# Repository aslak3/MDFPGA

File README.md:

# MDFPGA: a HUB75 display controller base board using a Pi Pico W and an iCE40UP5K

A [schematic](MDFPGA.pdf) is included here, along with the [KiCAD](https://www.kicad.org)
data files, which are in KiCAD 6 format.

## PCB design

The PCB is a 4 layer board easily built by any random PCB house.

## Project overview

This board is the hardware for my Matrix Display project, which is spread across three repos: this one, [a repo holding the Pico W firmware](https://github.com/aslak3/matrix-display), and [an optional one that holds the HUB75 display controller](https://github.com/aslak3/hub75-controller), which is implemented in Verilog.

Once up and running, you will have a 64 x 32 LED matrix display, presenting information from your Home Assistant system or, in theory, any other system that publish data in a suitable format via MQTT.

## Hardware description

* Power via 5V barrel jack
* A Pi Pico W (obviously)
* A [DS3231](https://www.analog.com/media/en/technical-documentation/data-sheets/DS3231.pdf) (PDF) I2C Real Time Clock
  * CR122t battery backup
* IDC16 HUB75 connector attached to the Pico W
* Buzzer
* iCE40UP FPGA
  * [N25Q32A](https://www.mouser.co.uk/datasheet/2/12/Micron_Datasheet_N25Q032A_RevJ-1880047.pdf) (PDF) 32MBit SPI Flash
  * IDC16 HUB75 connector attached to the FPGA
  * LED

## Possible gotchas

The board revision included here fixes some minor issues I found in the board I use on a daily basis:

* The CR1225 conenctor has been moved a few mm to make it easier to insert and remove the battery.
* The screw terminals, which power the HUB75 panel, have been pointed in the oposite direction, making them easier to access.
* More vias have been added around the 1.2V power pin on the linear regulator.

## References

* [Matrix Display](https://github.com/aslak3/matrix-display) The projects main repository. which holds the firmware source code.
* [HUB75 Controller](https://github.com/aslak3/hub75-controller) A HUB75 LED matrix controller implemented in Verilog.

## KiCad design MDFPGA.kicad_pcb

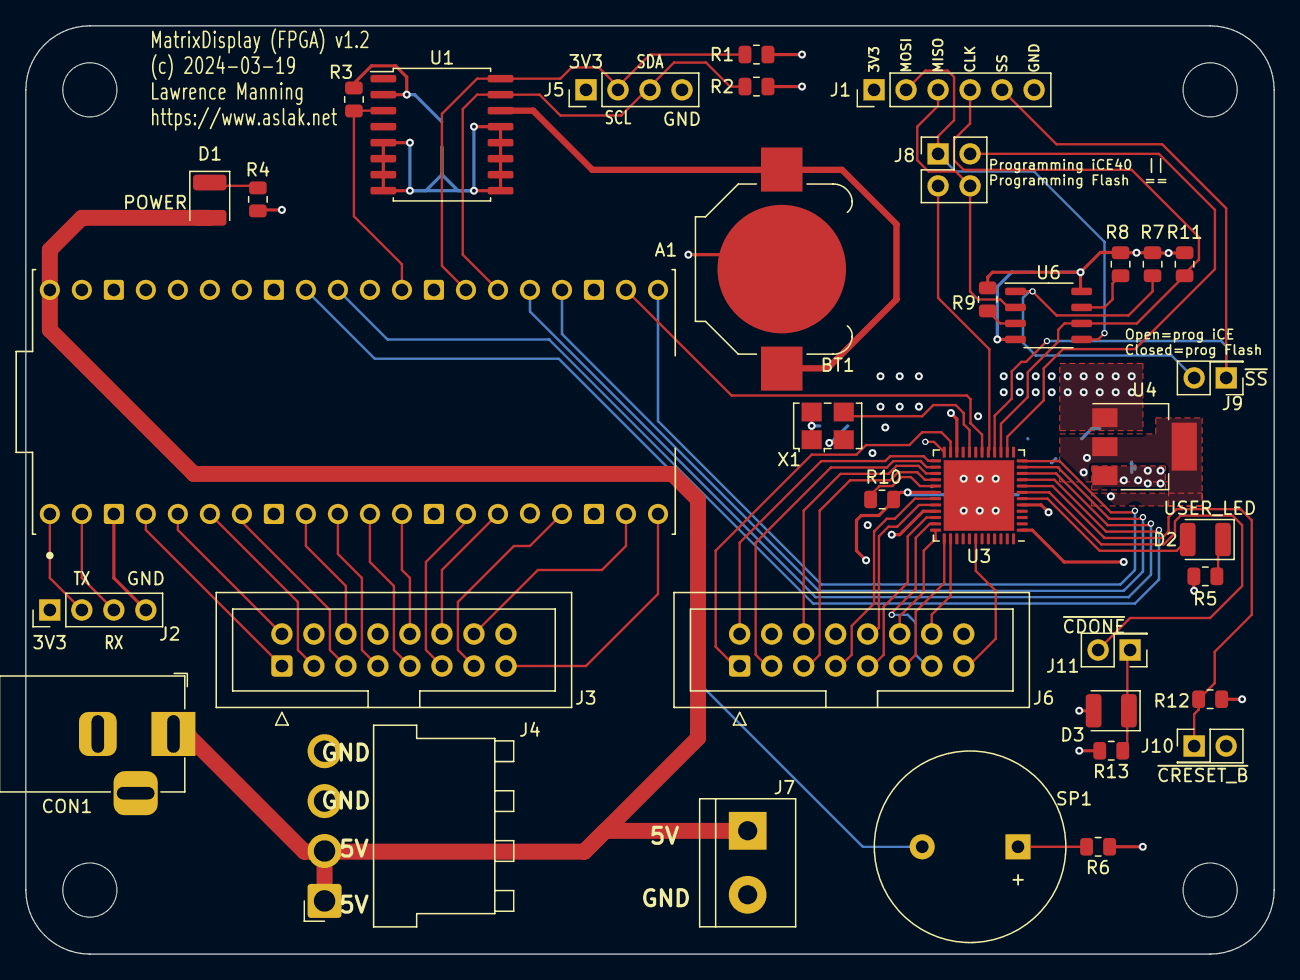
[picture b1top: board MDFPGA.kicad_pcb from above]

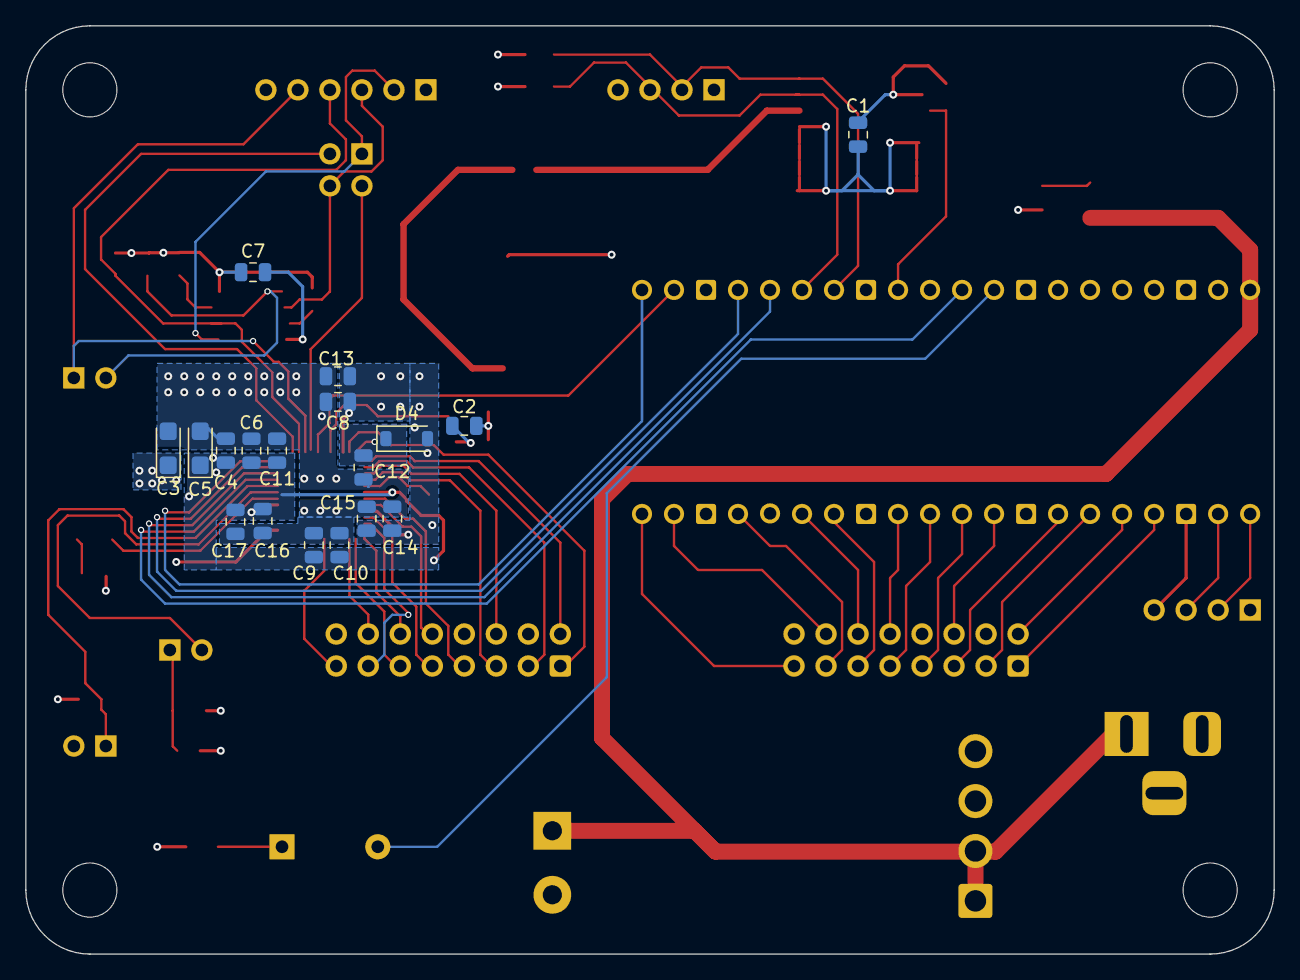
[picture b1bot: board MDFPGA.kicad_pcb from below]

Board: 4 copper layers, 99.1 x 73.7 mm, 58 parts (18 on the bottom side), 61 nets.

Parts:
A1: SC0918; MODULE_SC0918
BT1: Battery_Cell; BatteryHolder_Keystone_3000_1x12mm
C1, C2, C4, C7, C8, C11, C12, C14, C16: 0.1u; C_0805_2012Metric
C3, C5: 10u; CP_EIA-3216-10_Kemet-I
C6, C13, C15, C17: 10n; C_0805_2012Metric
C9: 10u; C_0805_2012Metric
C10: 100n; C_0805_2012Metric
CON1: POWERLJACK; BarrelJack_Horizontal
D1, D2: POWERLED; LED_1210_3225Metric
D3: CDONE_LED; LED_1210_3225Metric
D4: MBR130; D_SOD-123
H1, H2, H3, H4: HOLE; MountingHole_4.3mm_M4
J1: Conn_01x06; PinHeader_1x06_P2.54mm_Vertical
J2, J5: Conn_01x04; PinHeader_1x04_P2.54mm_Vertical
J3, J6: Conn_02x08_Odd_Even; IDC-Header_2x08_P2.54mm_Vertical
J4: Conn_01x04; JST_VH_B4PS-VH_1x04_P3.96mm_Horizontal
J7: Screw_Terminal_01x02; TerminalBlock_bornier-2_P5.08mm
J8: Conn_02x02_Odd_Even; PinHeader_2x02_P2.54mm_Vertical
J9, J10, J11: Conn_02x01; PinHeader_2x01_P2.54mm_Vertical
R1, R2, R3: 4.7K; R_0805_2012Metric
R4, R5, R6, R13: 1K; R_0805_2012Metric
R7, R8, R9, R11, R12: 10K; R_0805_2012Metric
R10: 100; R_0805_2012Metric
SP1: BUZZER; Buzzer_15x7.5RM7.6
U1: DS3231M; SOIC-16W_7.5x10.3mm_P1.27mm
U3: ICE40UP5K-SG48ITR; QFN-48-1EP_7x7mm_P0.5mm_EP5.6x5.6mm
U4: AZ1117-1.2; SOT-223-3_TabPin2
U6: N25Q032A13ESC40F; SOP-8_3.9x4.9mm_P1.27mm
X1: 50MHz; Oscillator_SMD_SeikoEpson_SG8002LB-4Pin_5.0x3.2mm

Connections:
+1V2: C4.1, C5.1, C6.1, C9.1, C10.1, C11.1, C16.1, C17.1, R10.1, U3.5 (VCC), U3.30 (VCC), U4.2 (VO)
+3V3: A1.36 (3V3_OUT), C1.1, C2.1, C3.1, C7.1, C8.1, C13.1, C14.1, C15.1, D3.2 (A), D4.2 (A), J1.1, J2.1, J5.1, R1.1, R2.1, R3.1, R7.1, R8.1, R9.1, R11.1, R12.1, U1.2 (VCC), U3.1 (VCCIO_2), U3.22 (SPI_VCCIO1), U3.33 (VCCIO_0), U4.3 (VI), U6.8 (VCC), X1.1 (OE), X1.4 (Vcc)
+5V: A1.40 (VBUS), CON1.1, D1.2 (A), J4.1, J4.2, J7.1
/ADDRA: A1.11 (GP8), J3.9
/ADDRB: A1.12 (GP9), J3.10
/ADDRC: A1.14 (GP10), J3.11
/ADDRD: A1.15 (GP11), J3.12
/BLUE1: A1.6 (GP4), J3.3
/BLUE2: A1.10 (GP7), J3.7
/BUZZER: A1.32 (GP27), SP1.2
/CLK: A1.17 (GP13), J3.13
/FPGA/ADDRA: J6.9, U3.34 (IOT_44b)
/FPGA/ADDRB: J6.10, U3.32 (IOT_43a)
/FPGA/ADDRC: J6.11, U3.37 (IOT_45a_G1)
/FPGA/ADDRD: J6.12, U3.36 (IOT_48b)
/FPGA/BLUE1: J6.3, U3.26 (IOT_39a)
/FPGA/BLUE2: J6.7, U3.31 (IOT_42b)
/FPGA/CDONE: J11.2, U3.7 (CDONE)
/FPGA/CLK: J6.13, U3.35 (IOT_46b_G0)
/FPGA/FLASH_MISO: J1.3, J8.4, U6.2 (DO(IO1))
/FPGA/FLASH_MOSI: J1.2, J8.1, U6.5 (DI(IO0))
/FPGA/GLOBAL_CLK: U3.20 (IOB_25b_G3), X1.3 (OUT)
/FPGA/GREEN1: J6.2, U3.25 (IOT_36b)
/FPGA/GREEN2: J6.6, U3.27 (IOT_38b)
/FPGA/ICE_MISO: J8.2, U3.14 (IOB_32a_SPI_SO)
/FPGA/ICE_MOSI: J8.3, U3.17 (IOB_33b_SPI_SI)
/FPGA/ICE_SCK: J1.4, R11.2, U3.15 (IOB_34a_SPI_SCK), U6.6 (CLK)
/FPGA/ICE_SS: J1.5, J9.1, U3.16 (IOB_35b_SPI_SS)
/FPGA/LATCH: J6.14, U3.38 (IOT_50b)
/FPGA/OE: J6.15, U3.42 (IOT_51a)
/FPGA/RED1: J6.1, U3.23 (IOT_37a)
/FPGA/RED2: J6.5, U3.28 (IOT_41a)
/FPGA/VPP_2V5: C12.1, D4.1 (K), U3.24 (VPP_2V5)
/FPGA/~CRESET_B: J10.1, R12.2, U3.8 (~CRESET)
/GREEN1: A1.5 (GP3), J3.2
/GREEN2: A1.9 (GP6), J3.6
/LATCH: A1.19 (GP14), J3.14
/OE: A1.20 (GP15), J3.15
/RED1: A1.4 (GP2), J3.1
/RED2: A1.7 (GP5), J3.5
/RTCSQWAVE: A1.29 (GP22), R3.2, U1.3 (~INT/SQW)
/SCL: A1.27 (GP21), J5.2, R1.2, U1.16 (SCL)
/SDA: A1.26 (GP20), J5.3, R2.2, U1.15 (SDA)
/UART0_RX: A1.2 (GP1), J2.3
/UART0_TX: A1.1 (GP0), J2.2
/VBAT: BT1.1 (+), U1.14 (VBAT)
CTRL_CLK: A1.24 (GP18), U3.11 (IOB_20a)
CTRL_MISO: A1.21 (GP16), U3.12 (IOB_22a)
CTRL_MOSI: A1.25 (GP19), U3.10 (IOB_18a)
GND: A1.3 (GND), A1.8 (GND), A1.13 (GND), A1.18 (GND), A1.23 (GND), A1.28 (GND), A1.33 (AGND), A1.38 (GND), BT1.2 (-), C1.2, C2.2, C3.2, C4.2, C5.2, C6.2, C7.2, C8.2, C9.2, C10.2, C11.2, C12.2, C13.2, C14.2, C15.2, C16.2, C17.2, CON1.2, CON1.3, J1.6, J2.4, J3.4, J3.8, J3.16, J4.3, J4.4, J5.4, J6.4, J6.8, J6.16, J7.2, J10.2, R4.2, R5.2, R6.1, R13.2, U1.5 (GND), U1.6 (GND), U1.7 (GND), U1.8 (GND), U1.9 (GND), U1.10 (GND), U1.11 (GND), U1.12 (GND), U1.13 (GND), U3.49 (GND), U4.1 (GND), U6.4 (GND), X1.2 (GND)
unnamed: D1.1 (K), R4.1
unnamed: D2.1 (K), R5.1
unnamed: D3.1 (K), J11.1, R13.1
unnamed: J9.2, R7.2, U6.1 (~CS)
unnamed: R6.2, SP1.1
unnamed: R10.2, U3.29 (VCCPLL)
unnamed: R9.2, U6.3 (IO2)
unnamed: R8.2, U6.7 (IO3)
USER_LED: D2.2 (A), U3.6 (IOB_13b)
~CTRL_RESET: A1.31 (GP26), U3.9 (IOB_16a)
~CTRL_SS: A1.22 (GP17), U3.18 (IOB_31b)

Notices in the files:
MDFPGA.kicad_pcb:
(c) 2024-03-19
